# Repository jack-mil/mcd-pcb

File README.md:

# M68000 Single Board Computer PCB #

Kicad project files for pcb design

Designed with Kicad V6

Also included in `vhdl/` is the code for control logic in the CPLD

v1.0.0 goes with the monitor software developed in the [mcd-asm repository](https://github.com/jack-mil/mcd-asm/).

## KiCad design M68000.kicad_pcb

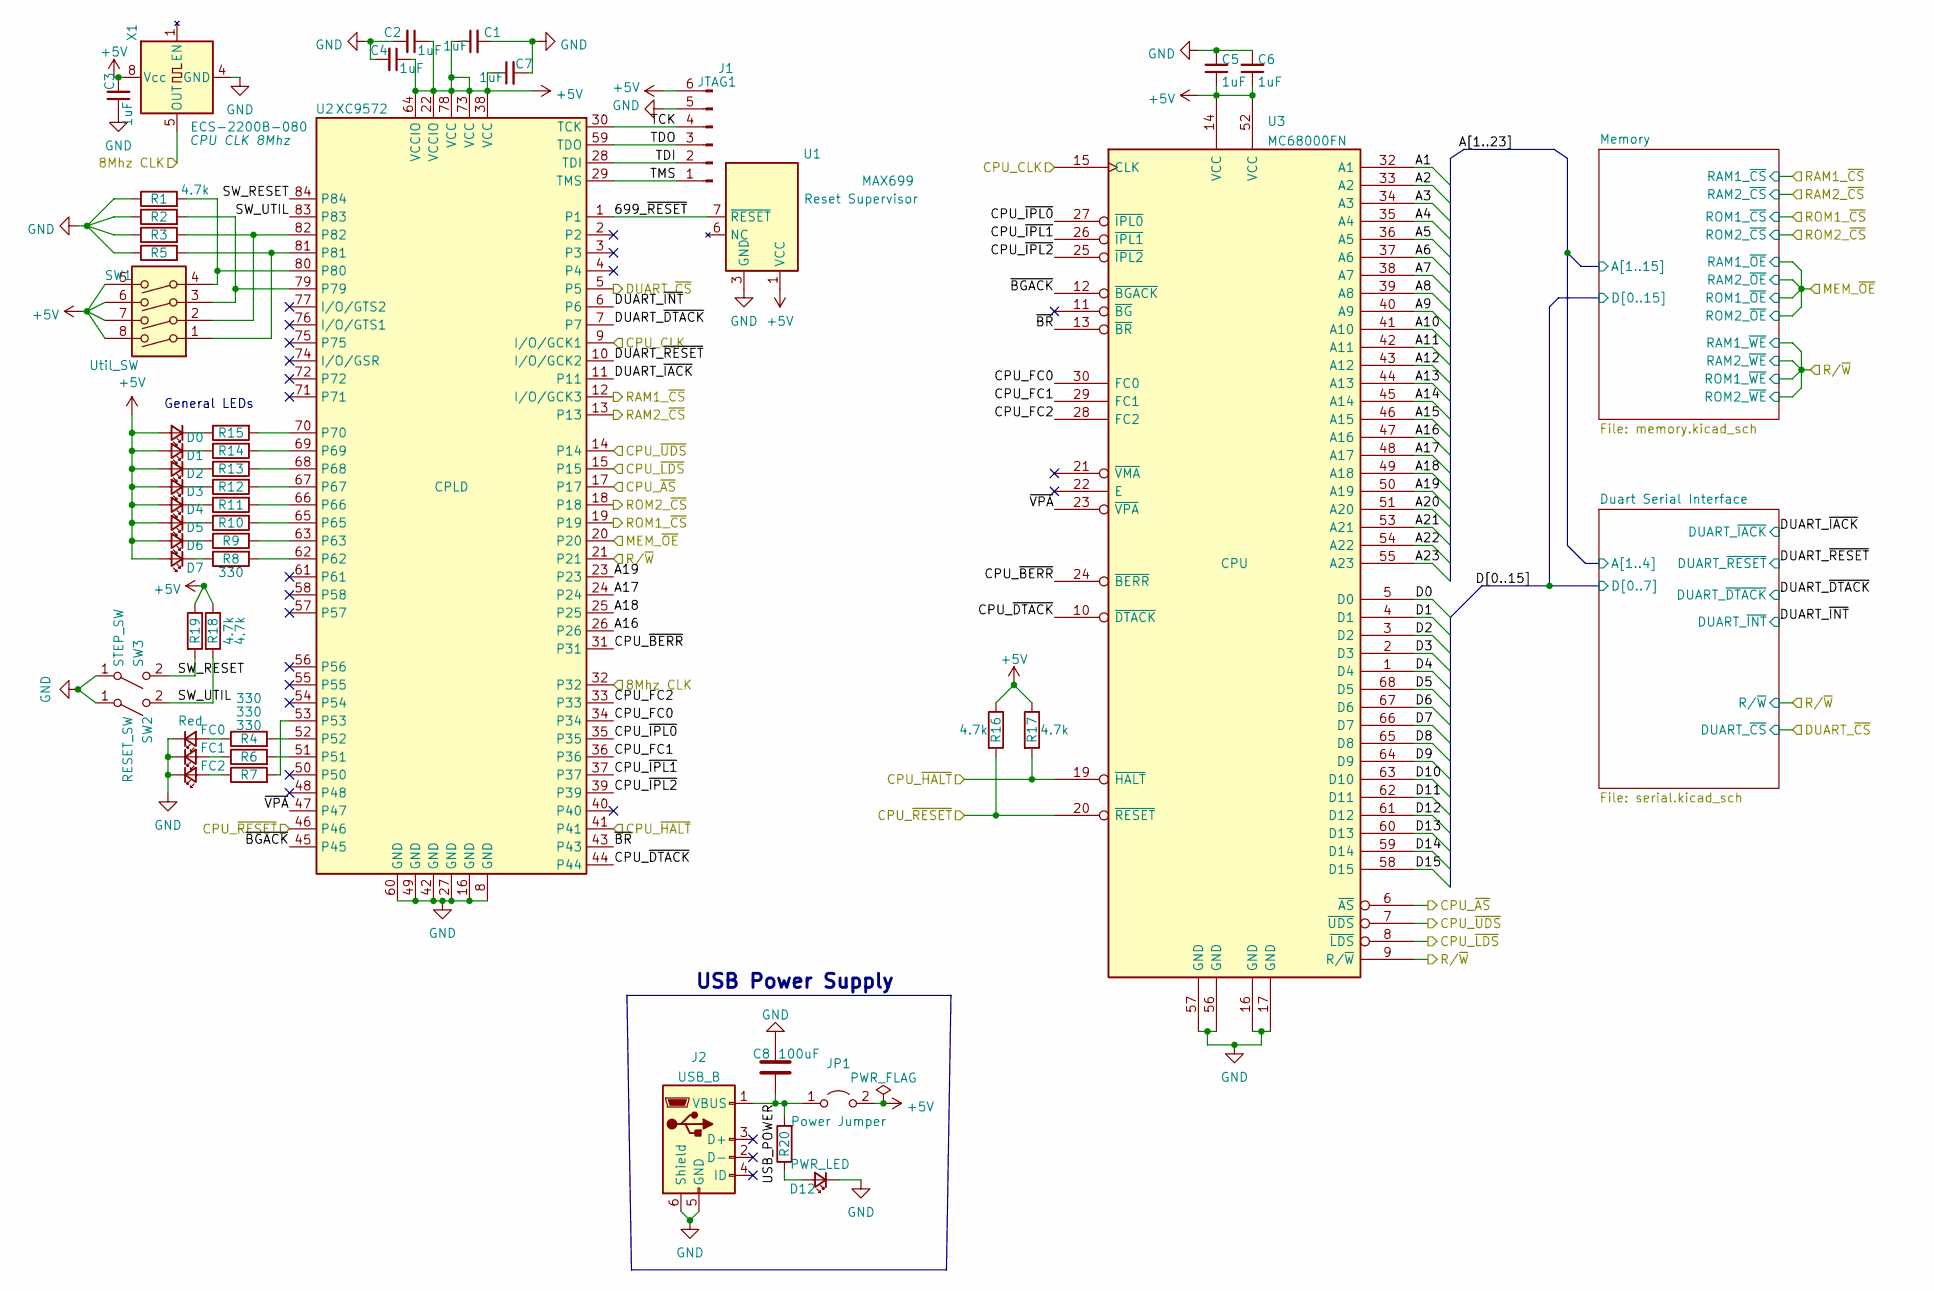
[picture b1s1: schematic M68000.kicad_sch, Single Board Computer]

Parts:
C1, C2, C3, C4, C5, C6, C7: 1uF; C_0805_2012Metric_Pad1.18x1.45mm_HandSolder
C8: 100uF; C_1210_3225Metric_Pad1.33x2.70mm_HandSolder
D0, D1, D2, D3: Green; LED_0805_2012Metric_Pad1.15x1.40mm_HandSolder
D4, D5, D6, D7: Blue; LED_0805_2012Metric_Pad1.15x1.40mm_HandSolder
D12: PWR_LED; LED_0805_2012Metric_Pad1.15x1.40mm_HandSolder
FC0, FC1, FC2: Red; LED_0805_2012Metric_Pad1.15x1.40mm_HandSolder
J1: JTAG1; JTAG PinHeader_1x06_P2.54mm_Vertical
J2: USB_B; USB_Micro-B_CS5A-NF
JP1: Power Jumper; PinHeader_1x02_P2.54mm_Vertical
R1, R2, R3, R5, R16, R17, R18, R19: 4.7k; R_0805_2012Metric_Pad1.20x1.40mm_HandSolder
R4, R6, R7, R8, R9, R10, R11, R12, R13, R14, R15, R20: 330; R_0805_2012Metric_Pad1.20x1.40mm_HandSolder
SW1: Util_SW; SW_DIP_SPSTx04_Slide_6.7x11.72mm_W8.61mm_P2.54mm_LowProfile
SW2: RESET_SW; SW_PUSH_6mm
SW3: STEP_SW; SW_PUSH_6mm
U1: MAX699; DIP-8_W7.62mm_LongPads
U2: XC9572; PLCC-84_THT-Socket
U3: MC68000FN; PLCC-68_THT-Socket
X1: ECS-2200B-080; Oscillator_DIP-8_LargePads

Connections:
+5V: C1.1, C2.1, C3.2, C4.1, C5.1, C6.1, C7.1, D0.2 (A), D1.2 (A), D2.2 (A), D3.2 (A), D4.2 (A), D5.2 (A), D6.2 (A), D7.2 (A), J1.6, JP1.2 (B), R16.1, R17.1, R18.1, R19.1, SW1.5, SW1.6, SW1.7, SW1.8, U1.1 (VCC), U1.2 (VCC), U2.22 (VCCIO), U2.38 (VCC), U2.64 (VCCIO), U2.73 (VCC), U2.78 (VCC), U3.14 (VCC), U3.52 (VCC), X1.8 (Vcc); also elsewhere on the board
/8Mhz CLK: U2.32, X1.5 (OUT)
/699_~RESET: U1.7 (~RESET), U2.1
/A1: U3.32 (A1); also elsewhere on the board
/A2: U3.33 (A2); also elsewhere on the board
/A3: U3.34 (A3); also elsewhere on the board
/A4: U3.35 (A4); also elsewhere on the board
/A5: U3.36 (A5); also elsewhere on the board
/A6: U3.37 (A6); also elsewhere on the board
/A7: U3.38 (A7); also elsewhere on the board
/A8: U3.39 (A8); also elsewhere on the board
/A9: U3.40 (A9); also elsewhere on the board
/A10: U3.41 (A10); also elsewhere on the board
/A11: U3.42 (A11); also elsewhere on the board
/A12: U3.43 (A12); also elsewhere on the board
/A13: U3.44 (A13); also elsewhere on the board
/A14: U3.45 (A14); also elsewhere on the board
/A15: U3.46 (A15); also elsewhere on the board
/A16: U2.26, U3.47 (A16)
/A17: U2.24, U3.48 (A17)
/A18: U2.25, U3.49 (A18)
/A19: U2.23, U3.50 (A19)
/A20: U3.51 (A20)
/A21: U3.53 (A21)
/A22: U3.54 (A22)
/A23: U3.55 (A23)
/CPU_CLK: U2.9 (I/O/GCK1), U3.15 (CLK)
/CPU_FC0: U2.34, U3.30 (FC0)
/CPU_FC1: U2.36, U3.29 (FC1)
/CPU_FC2: U2.33, U3.28 (FC2)
/CPU_~AS: U2.17, U3.6 (~AS)
/CPU_~BERR: U2.31, U3.24 (~BERR)
/CPU_~DTACK: U2.44, U3.10 (~DTACK)
/CPU_~HALT: R17.2, U2.41, U3.19 (~HALT)
/CPU_~IPL0: U2.35, U3.27 (~IPL0)
/CPU_~IPL1: U2.37, U3.26 (~IPL1)
/CPU_~IPL2: U2.39, U3.25 (~IPL2)
/CPU_~LDS: U2.15, U3.8 (~LDS)
/CPU_~RESET: R16.2, U2.46, U3.20 (~RESET)
/CPU_~UDS: U2.14, U3.7 (~UDS)
/D0: U3.5 (D0); also elsewhere on the board
/D1: U3.4 (D1); also elsewhere on the board
/D2: U3.3 (D2); also elsewhere on the board
/D3: U3.2 (D3); also elsewhere on the board
/D4: U3.1 (D4); also elsewhere on the board
/D5: U3.68 (D5); also elsewhere on the board
/D6: U3.67 (D6); also elsewhere on the board
/D7: U3.66 (D7); also elsewhere on the board
/D8: U3.65 (D8); also elsewhere on the board
/D9: U3.64 (D9); also elsewhere on the board
/D10: U3.63 (D10); also elsewhere on the board
/D11: U3.62 (D11); also elsewhere on the board
/D12: U3.61 (D12); also elsewhere on the board
/D13: U3.60 (D13); also elsewhere on the board
/D14: U3.59 (D14); also elsewhere on the board
/D15: U3.58 (D15); also elsewhere on the board
/DUART_~CS: U2.5; also elsewhere on the board
/DUART_~DTACK: U2.7; also elsewhere on the board
/DUART_~IACK: U2.11; also elsewhere on the board
/DUART_~INT: U2.6; also elsewhere on the board
/DUART_~RESET: U2.10 (I/O/GCK2); also elsewhere on the board
/MEM_~OE: U2.20; also elsewhere on the board
/RAM1_~CS: U2.12 (I/O/GCK3); also elsewhere on the board
/RAM2_~CS: U2.13; also elsewhere on the board
/ROM1_~CS: U2.19; also elsewhere on the board
/ROM2_~CS: U2.18; also elsewhere on the board
/R/~W: U2.21, U3.9 (R/~W); also elsewhere on the board
/SW_RESET: R19.2, SW3.2 (B), U2.84
/SW_UTIL: R18.2, SW2.2 (B), U2.83
/TCK: J1.4, U2.30 (TCK)
/TDI: J1.2, U2.28 (TDI)
/TDO: J1.3, U2.59 (TDO)
/TMS: J1.1, U2.29 (TMS)
/USB_POWER: C8.1, J2.1 (VBUS), JP1.1 (A), R20.2
/~BGACK: U2.45, U3.12 (~BGACK)
/~BR: U2.43, U3.13 (~BR)
/~VPA: U2.47, U3.23 (~VPA)
GND: C1.2, C2.2, C3.1, C4.2, C5.2, C6.2, C7.2, C8.2, D12.1 (K), FC0.1 (K), FC1.1 (K), FC2.1 (K), J1.5, J2.5 (GND), J2.6 (Shield), R1.1, R2.1, R3.1, R5.1, SW2.1 (A), SW3.1 (A), U1.3 (GND), U1.4 (GND), U1.8 (GND), U2.8 (GND), U2.16 (GND), U2.27 (GND), U2.42 (GND), U2.49 (GND), U2.60 (GND), U3.16 (GND), U3.17 (GND), U3.56 (GND), U3.57 (GND), X1.4 (GND); also elsewhere on the board
unnamed: D0.1 (K), R15.1
unnamed: D1.1 (K), R14.1
unnamed: D2.1 (K), R13.1
unnamed: D3.1 (K), R12.1
unnamed: D4.1 (K), R11.1
unnamed: D5.1 (K), R10.1
unnamed: D6.1 (K), R9.1
unnamed: D7.1 (K), R8.1
unnamed: D12.2 (A), R20.1
unnamed: FC0.2 (A), R4.1
unnamed: FC1.2 (A), R6.1
unnamed: FC2.2 (A), R7.1
unnamed: R1.2, SW1.4, U2.80
unnamed: R2.2, SW1.3, U2.79
unnamed: R3.2, SW1.2, U2.82
unnamed: R4.2, U2.52
unnamed: R5.2, SW1.1, U2.81
unnamed: R6.2, U2.51
unnamed: R7.2, U2.53
unnamed: R8.2, U2.62
unnamed: R9.2, U2.63
unnamed: R10.2, U2.65
unnamed: R11.2, U2.66
unnamed: R12.2, U2.67
unnamed: R13.2, U2.68
unnamed: R14.2, U2.69
unnamed: R15.2, U2.70

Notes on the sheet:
General LEDs
USB Power Supply

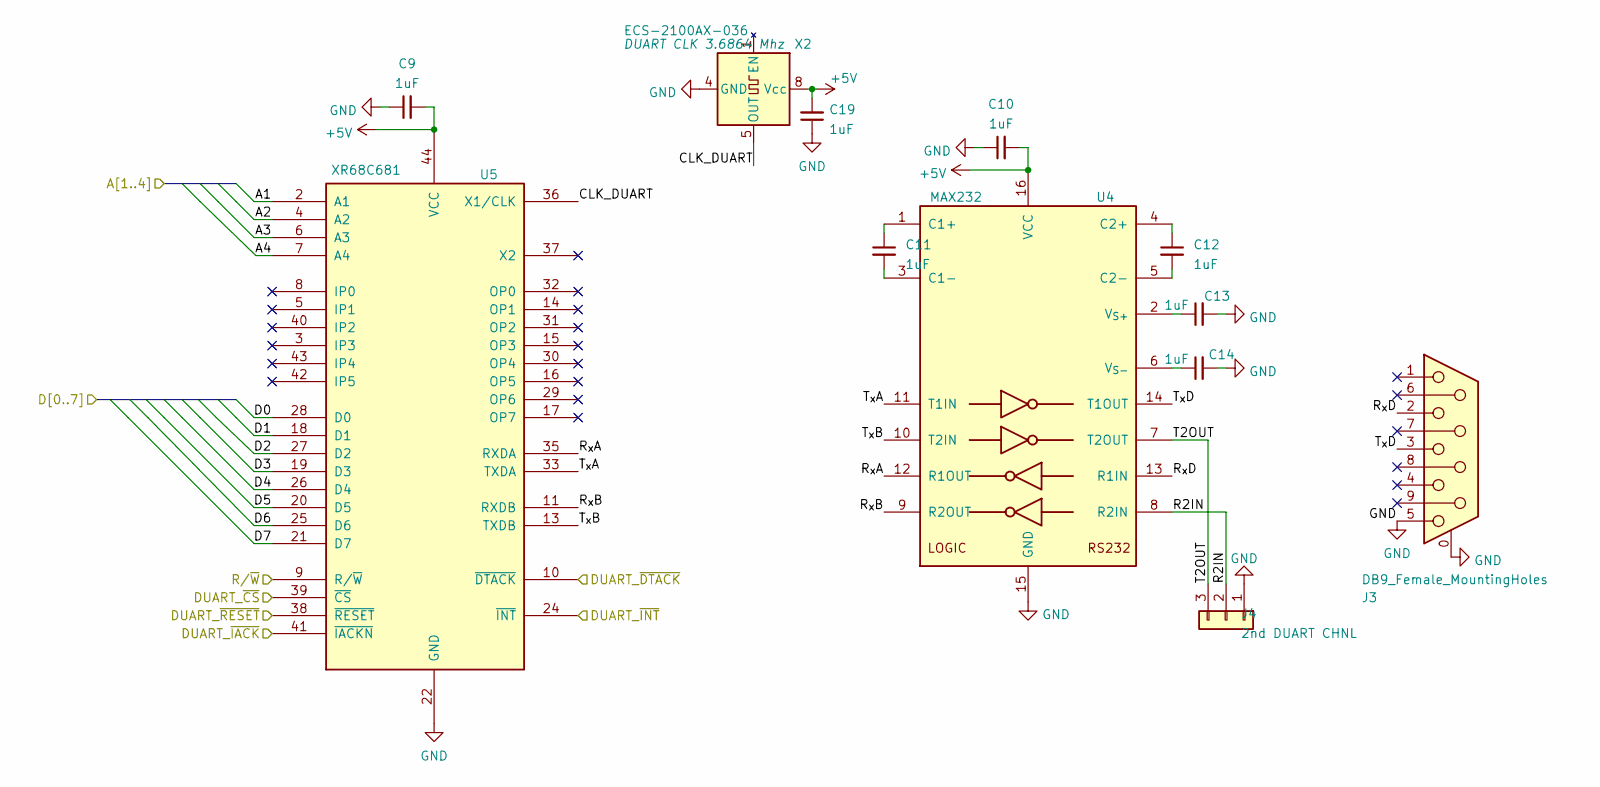
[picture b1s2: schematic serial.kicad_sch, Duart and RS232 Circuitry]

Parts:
C9, C10, C11, C12, C13, C14, C19: 1uF; C_0805_2012Metric_Pad1.18x1.45mm_HandSolder
J3: DB9_Female_MountingHoles; DSUB-9_Female_Horizontal_P2.77x2.84mm_EdgePinOffset7.70mm_H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
J4: 2nd DUART CHNL; PinHeader_1x03_P2.54mm_Vertical
U4: MAX232; DIP-16_W7.62mm_Socket
U5: XR68C681; PLCC-44_THT-Socket
X2: ECS-2100AX-036; Oscillator_DIP-8_LargePads

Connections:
+5V: C9.2, C10.2, C19.2, U4.16 (VCC), U5.44 (VCC), X2.8 (Vcc); also elsewhere on the board
/A1: U5.2 (A1); also elsewhere on the board
/A2: U5.4 (A2); also elsewhere on the board
/A3: U5.6 (A3); also elsewhere on the board
/A4: U5.7 (A4); also elsewhere on the board
/D0: U5.28 (D0); also elsewhere on the board
/D1: U5.18 (D1); also elsewhere on the board
/D2: U5.27 (D2); also elsewhere on the board
/D3: U5.19 (D3); also elsewhere on the board
/D4: U5.26 (D4); also elsewhere on the board
/D5: U5.20 (D5); also elsewhere on the board
/D6: U5.25 (D6); also elsewhere on the board
/D7: U5.21 (D7); also elsewhere on the board
/DUART_~CS: U5.39 (~CS); also elsewhere on the board
/DUART_~DTACK: U5.10 (~DTACK); also elsewhere on the board
/DUART_~IACK: U5.41 (~IACKN); also elsewhere on the board
/DUART_~INT: U5.24 (~INT); also elsewhere on the board
/DUART_~RESET: U5.38 (~RESET); also elsewhere on the board
/Duart Serial Interface/CLK_DUART: U5.36 (X1/CLK), X2.5 (OUT)
/Duart Serial Interface/R2IN: J4.2, U4.8 (R2IN)
/Duart Serial Interface/R_{x}A: U4.12 (R1OUT), U5.35 (RXDA)
/Duart Serial Interface/R_{x}B: U4.9 (R2OUT), U5.11 (RXDB)
/Duart Serial Interface/R_{x}D: J3.2, U4.13 (R1IN)
/Duart Serial Interface/T2OUT: J4.3, U4.7 (T2OUT)
/Duart Serial Interface/T_{x}A: U4.11 (T1IN), U5.33 (TXDA)
/Duart Serial Interface/T_{x}B: U4.10 (T2IN), U5.13 (TXDB)
/Duart Serial Interface/T_{x}D: J3.3, U4.14 (T1OUT)
/R/~W: U5.9 (R/~W); also elsewhere on the board
GND: C9.1, C10.1, C13.2, C14.2, C19.1, J3.0 (PAD), J3.5, J4.1, U4.15 (GND), U5.22 (GND), X2.4 (GND); also elsewhere on the board
unnamed: C11.1, U4.1 (C1+)
unnamed: C11.2, U4.3 (C1-)
unnamed: C12.1, U4.4 (C2+)
unnamed: C12.2, U4.5 (C2-)
unnamed: C13.1, U4.2 (V_{S+})
unnamed: C14.1, U4.6 (V_{S-})

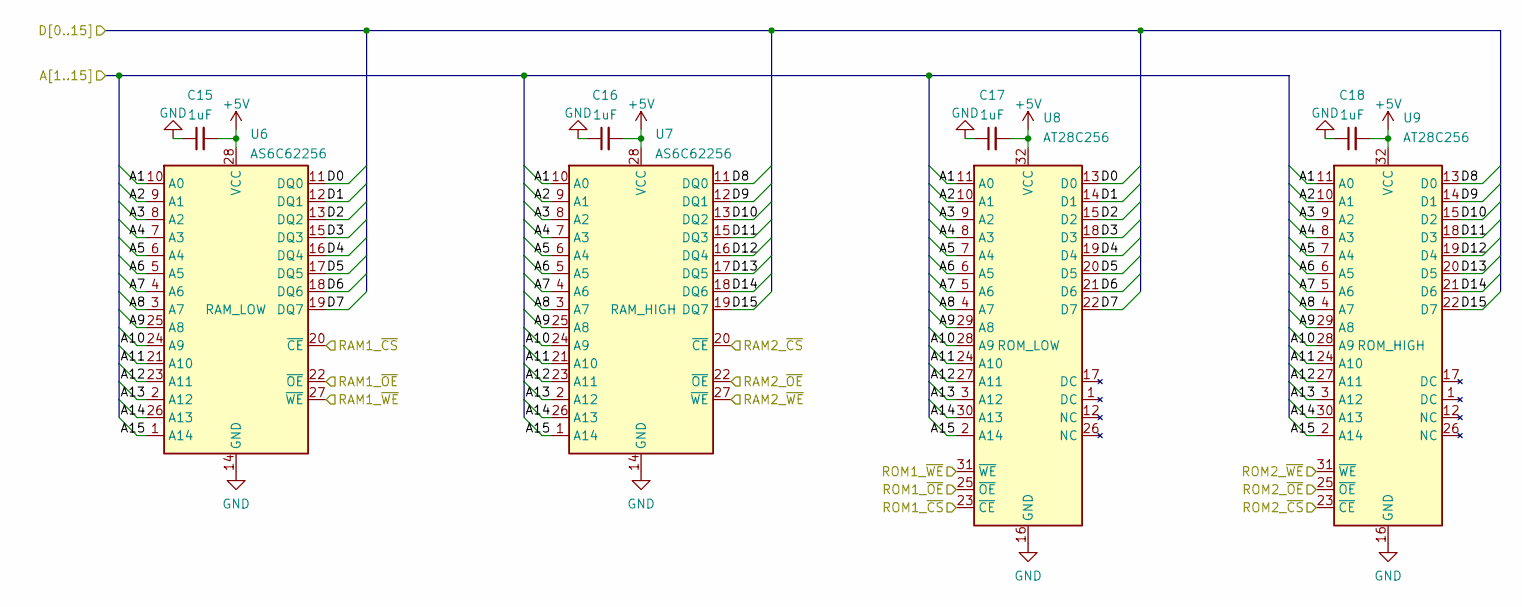
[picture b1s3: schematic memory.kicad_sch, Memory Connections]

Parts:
C15, C16, C17, C18: 1uF; C_0805_2012Metric_Pad1.18x1.45mm_HandSolder
U6, U7: AS6C62256; DIP-28_W15.24mm_Socket_LongPads
U8, U9: AT28C256; PLCC-32_THT-Socket

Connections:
+5V: C15.2, C16.2, C17.2, C18.2, U6.28 (VCC), U7.28 (VCC), U8.32 (VCC), U9.32 (VCC); also elsewhere on the board
/A1: U6.10 (A0), U7.10 (A0), U8.11 (A0), U9.11 (A0); also elsewhere on the board
/A2: U6.9 (A1), U7.9 (A1), U8.10 (A1), U9.10 (A1); also elsewhere on the board
/A3: U6.8 (A2), U7.8 (A2), U8.9 (A2), U9.9 (A2); also elsewhere on the board
/A4: U6.7 (A3), U7.7 (A3), U8.8 (A3), U9.8 (A3); also elsewhere on the board
/A5: U6.6 (A4), U7.6 (A4), U8.7 (A4), U9.7 (A4); also elsewhere on the board
/A6: U6.5 (A5), U7.5 (A5), U8.6 (A5), U9.6 (A5); also elsewhere on the board
/A7: U6.4 (A6), U7.4 (A6), U8.5 (A6), U9.5 (A6); also elsewhere on the board
/A8: U6.3 (A7), U7.3 (A7), U8.4 (A7), U9.4 (A7); also elsewhere on the board
/A9: U6.25 (A8), U7.25 (A8), U8.29 (A8), U9.29 (A8); also elsewhere on the board
/A10: U6.24 (A9), U7.24 (A9), U8.28 (A9), U9.28 (A9); also elsewhere on the board
/A11: U6.21 (A10), U7.21 (A10), U8.24 (A10), U9.24 (A10); also elsewhere on the board
/A12: U6.23 (A11), U7.23 (A11), U8.27 (A11), U9.27 (A11); also elsewhere on the board
/A13: U6.2 (A12), U7.2 (A12), U8.3 (A12), U9.3 (A12); also elsewhere on the board
/A14: U6.26 (A13), U7.26 (A13), U8.30 (A13), U9.30 (A13); also elsewhere on the board
/A15: U6.1 (A14), U7.1 (A14), U8.2 (A14), U9.2 (A14); also elsewhere on the board
/D0: U6.11 (DQ0), U8.13 (D0); also elsewhere on the board
/D1: U6.12 (DQ1), U8.14 (D1); also elsewhere on the board
/D2: U6.13 (DQ2), U8.15 (D2); also elsewhere on the board
/D3: U6.15 (DQ3), U8.18 (D3); also elsewhere on the board
/D4: U6.16 (DQ4), U8.19 (D4); also elsewhere on the board
/D5: U6.17 (DQ5), U8.20 (D5); also elsewhere on the board
/D6: U6.18 (DQ6), U8.21 (D6); also elsewhere on the board
/D7: U6.19 (DQ7), U8.22 (D7); also elsewhere on the board
/D8: U7.11 (DQ0), U9.13 (D0); also elsewhere on the board
/D9: U7.12 (DQ1), U9.14 (D1); also elsewhere on the board
/D10: U7.13 (DQ2), U9.15 (D2); also elsewhere on the board
/D11: U7.15 (DQ3), U9.18 (D3); also elsewhere on the board
/D12: U7.16 (DQ4), U9.19 (D4); also elsewhere on the board
/D13: U7.17 (DQ5), U9.20 (D5); also elsewhere on the board
/D14: U7.18 (DQ6), U9.21 (D6); also elsewhere on the board
/D15: U7.19 (DQ7), U9.22 (D7); also elsewhere on the board
/MEM_~OE: U6.22 (~OE), U7.22 (~OE), U8.25 (~OE), U9.25 (~OE); also elsewhere on the board
/RAM1_~CS: U6.20 (~CE); also elsewhere on the board
/RAM2_~CS: U7.20 (~CE); also elsewhere on the board
/ROM1_~CS: U8.23 (~CE); also elsewhere on the board
/ROM2_~CS: U9.23 (~CE); also elsewhere on the board
/R/~W: U6.27 (~WE), U7.27 (~WE), U8.31 (~WE), U9.31 (~WE); also elsewhere on the board
GND: C15.1, C16.1, C17.1, C18.1, U6.14 (GND), U7.14 (GND), U8.16 (GND), U9.16 (GND); also elsewhere on the board

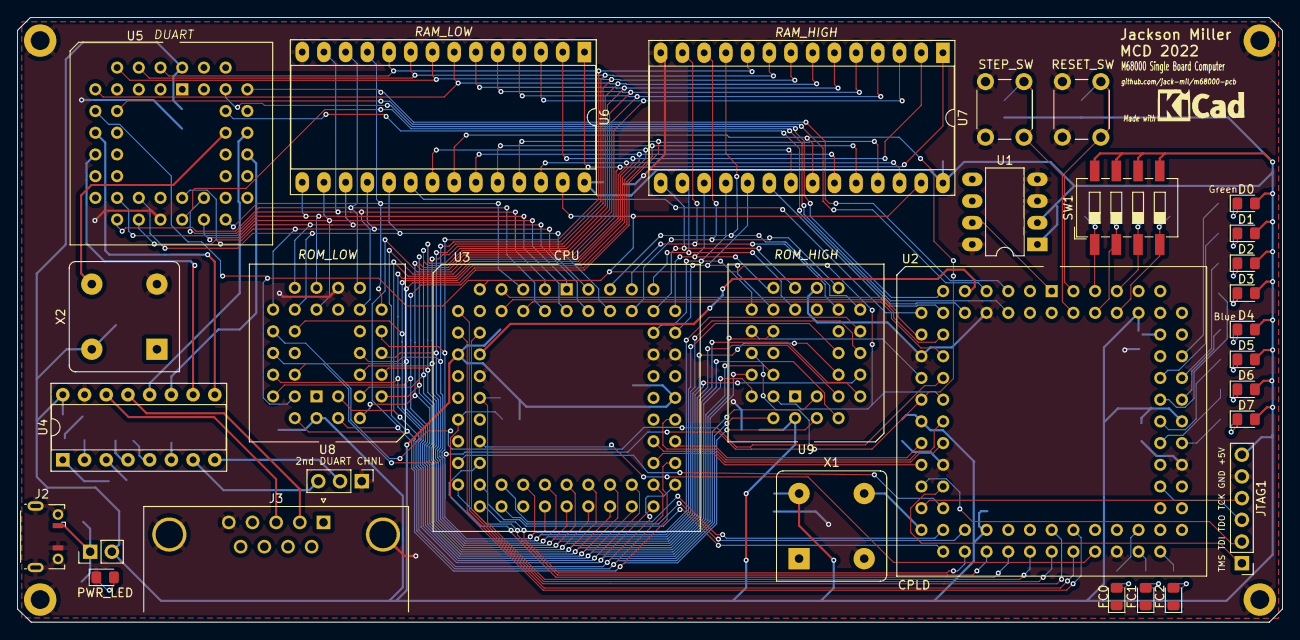
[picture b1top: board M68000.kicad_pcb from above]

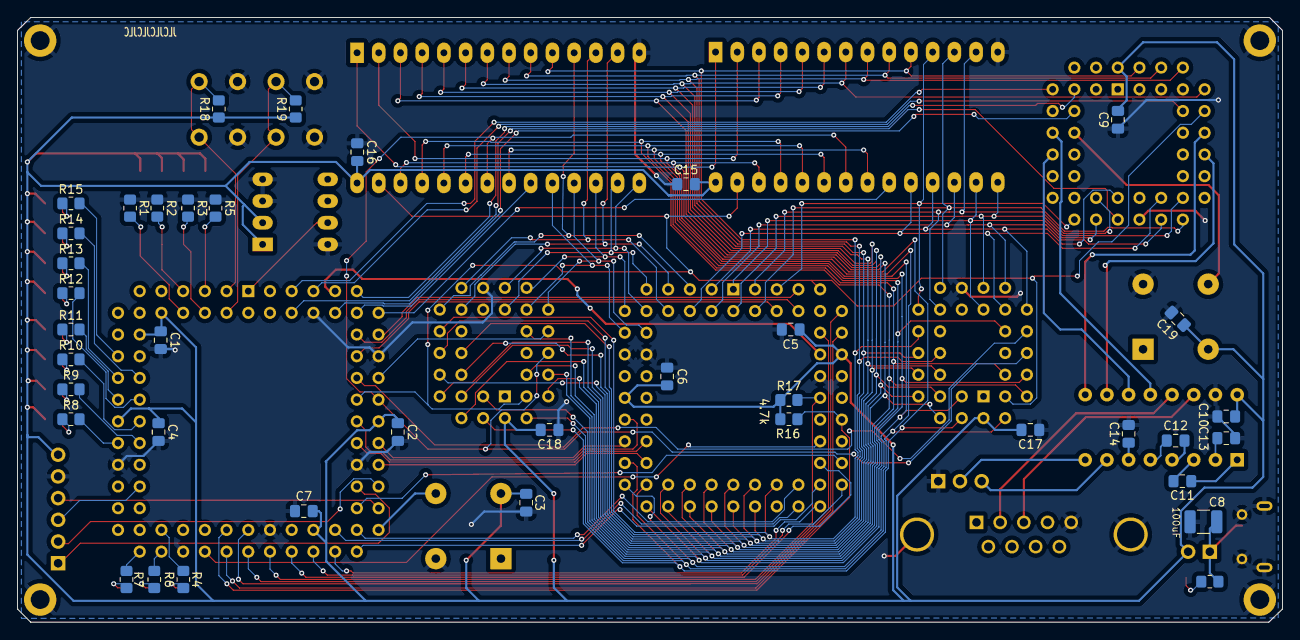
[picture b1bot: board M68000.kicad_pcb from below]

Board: 2 copper layers, 148.0 x 70.8 mm, 70 parts (39 on the bottom side), 116 nets.

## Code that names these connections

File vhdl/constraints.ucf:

NET DUART_CS LOC=P5;
NET DUART_INT LOC=P6;
NET DUART_DTACK LOC=P7;
NET DUART_RESET LOC=P10;
NET DUART_IACK LOC=P11;

NET CLK_IN LOC=P32;

NET SUP_RESET LOC=P1;

NET CPU_CLK LOC=P9;
NET CPU_HALT LOC=P41;
NET CPU_RESET LOC=P46;

NET RAML_CS LOC=P12;
NET RAMH_CS LOC=P13;
NET ROML_CS LOC=P19;
NET ROMH_CS LOC=P18;

NET MEM_OE LOC=P20;

NET CPU_AS LOC=P17;
NET CPU_RW LOC=P21;
NET CPU_UDS LOC=P14;
NET CPU_LDS LOC=P15;
NET CPU_DTACK LOC=P44;
NET CPU_BERR LOC=P31;

NET CPU_BR LOC=P43;
NET CPU_BGACK LOC=P45;

NET CPU_VPA LOC=P47;

NET ADDR<0> LOC=P26;
NET ADDR<1> LOC=P24;
NET ADDR<2> LOC=P25;
NET ADDR<3> LOC=P23;

NET CPU_FC<0> LOC=P34;
NET CPU_FC<1> LOC=P36;
NET CPU_FC<2> LOC=P33;

NET CPU_IPL<0> LOC=P35;
NET CPU_IPL<1> LOC=P37;
NET CPU_IPL<2> LOC=P39;


NET FC_LED<0> LOC=P52;
NET FC_LED<1> LOC=P51;
NET FC_LED<2> LOC=P53;

NET LED_G<0> LOC=P70;
NET LED_G<1> LOC=P69;
NET LED_G<2> LOC=P68;
NET LED_G<3> LOC=P67;

NET LED_B<0> LOC=P66;
NET LED_B<1> LOC=P65;
NET LED_B<2> LOC=P63;
NET LED_B<3> LOC=P62;

NET DIP_SW<0> LOC=P81;
NET DIP_SW<1> LOC=P82;
NET DIP_SW<2> LOC=P79;
NET DIP_SW<3> LOC=P80;

NET SW_RESET LOC=P83;
NET SW_UTIL LOC=P84;

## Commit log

2022-02-02 All parts and begin schematics
2022-02-23 Final PCB Layout
2022-02-27 Submitted to JLCPCB
2022-03-07 Cleanup fp and sym libraries
2022-03-07 Rename Memory to match High/Low
2022-03-07 Add images to README
2022-04-13 PCB v1 final design
2022-04-18 Add VHDL control logic
